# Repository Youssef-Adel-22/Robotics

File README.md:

# Robotics
Line Follower Robot Hardware and software design

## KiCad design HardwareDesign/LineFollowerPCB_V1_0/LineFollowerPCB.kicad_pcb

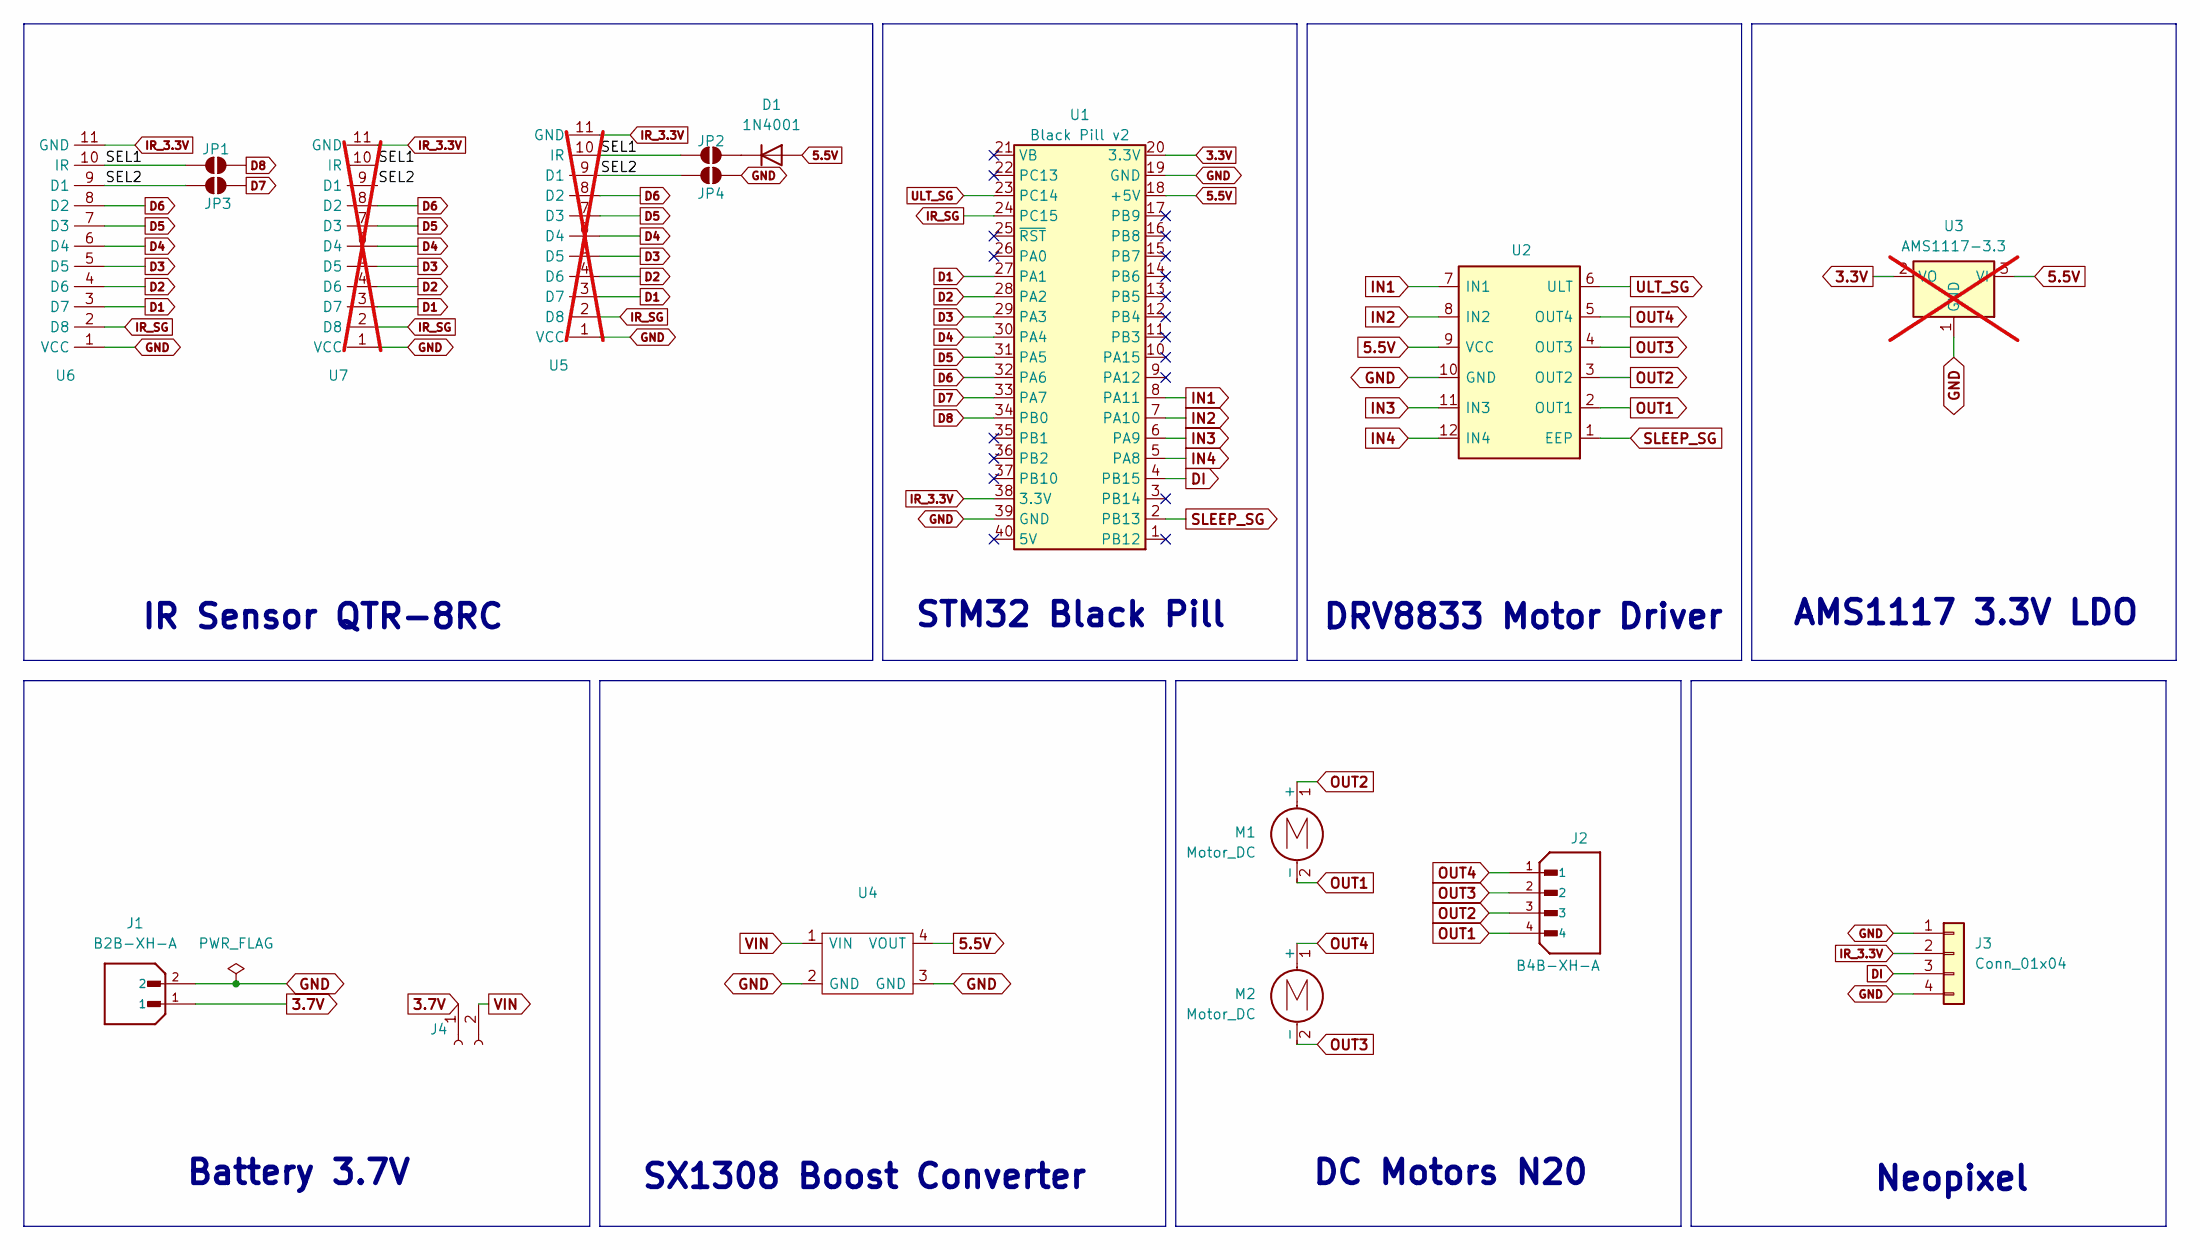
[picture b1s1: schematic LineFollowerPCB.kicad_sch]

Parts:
D1: 1N4001; D_DO-41_SOD81_P10.16mm_Horizontal
J1: B2B-XH-A; JST_B2B-XH-A; PARTREV N/A
J2: B4B-XH-A; JST_B4B-XH-A; PARTREV 7/4/21
J3: Conn_01x04; PinHeader_1x04_P2.54mm_Horizontal
J4: Conn_01x02_Socket; PinHeader_1x02_P2.54mm_Vertical
JP1, JP2, JP3, JP4: SolderJumper_3_Open; SolderJumper-2_P1.3mm_Open_RoundedPad1.0x1.5mm
M1, M2: Motor_DC; N20DCMotor
U1: Black Pill v2; Module_BlackPill_v2
U2: DRV8833
U3: AMS1117-3.3; PinHeader_1x03_P2.54mm_Vertical; not fitted
U4: SX1308
U5, U7: PinHeader_1x11_P2.54mm_Vertical; not fitted
U6: PinHeader_1x11_P2.54mm_Vertical

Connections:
3.3V: U1.20 (3.3V), U3.2 (VO)
3.7V: J1.1, J4.1
5.5V: D1.2 (A), U1.18 (+5V), U2.9 (VCC), U3.3 (VI), U4.4 (VOUT)
/SEL1: JP1.1 (A), JP2.2 (B), U5.10 (D8), U6.10 (D8), U7.10 (IR)
/SEL2: JP3.2 (B), JP4.1 (A), U5.9 (D7), U6.9 (D7), U7.9 (D1)
D1: U1.27 (PA1), U5.3 (D1), U6.3 (D1), U7.3 (D7)
D2: U1.28 (PA2), U5.4 (D2), U6.4 (D2), U7.4 (D6)
D3: U1.29 (PA3), U5.5 (D3), U6.5 (D3), U7.5 (D5)
D4: U1.30 (PA4), U5.6 (D4), U6.6 (D4), U7.6 (D4)
D5: U1.31 (PA5), U5.7 (D5), U6.7 (D5), U7.7 (D3)
D6: U1.32 (PA6), U5.8 (D6), U6.8 (D6), U7.8 (D2)
D7: JP3.1 (A), U1.33 (PA7)
D8: JP1.2 (B), U1.34 (PB0)
DI: J3.3, U1.4 (PB15)
GND: J1.2, J3.1, J3.4, JP4.2 (B), U1.19 (GND), U1.39 (GND), U2.10 (GND), U3.1 (GND), U4.2 (GND), U4.3 (GND), U5.1 (GND), U6.1 (GND), U7.1 (VCC)
IN1: U1.8 (PA11), U2.7 (IN1)
IN2: U1.7 (PA10), U2.8 (IN2)
IN3: U1.6 (PA9), U2.11 (IN3)
IN4: U1.5 (PA8), U2.12 (IN4)
IR_3.3V: J3.2, U1.38 (3.3V), U5.11 (VCC), U6.11 (VCC), U7.11 (GND)
IR_SG: U1.24 (PC15), U5.2 (IR), U6.2 (IR), U7.2 (D8)
unnamed: D1.1 (K), JP2.1 (A)
OUT1: J2.4, M1.2 (-), U2.2 (OUT1)
OUT2: J2.3, M1.1 (+), U2.3 (OUT2)
OUT3: J2.2, M2.2 (-), U2.4 (OUT3)
OUT4: J2.1, M2.1 (+), U2.5 (OUT4)
SLEEP_SG: U1.2 (PB13), U2.1 (EEP)
ULT_SG: U1.23 (PC14), U2.6 (ULT)
VIN: J4.2, U4.1 (VIN)

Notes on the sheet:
AMS1117 3.3V LDO
Neopixel
IR Sensor QTR-8RC
Battery 3.7V
STM32 Black Pill
SX1308 Boost Converter
DRV8833 Motor Driver
DC Motors N20

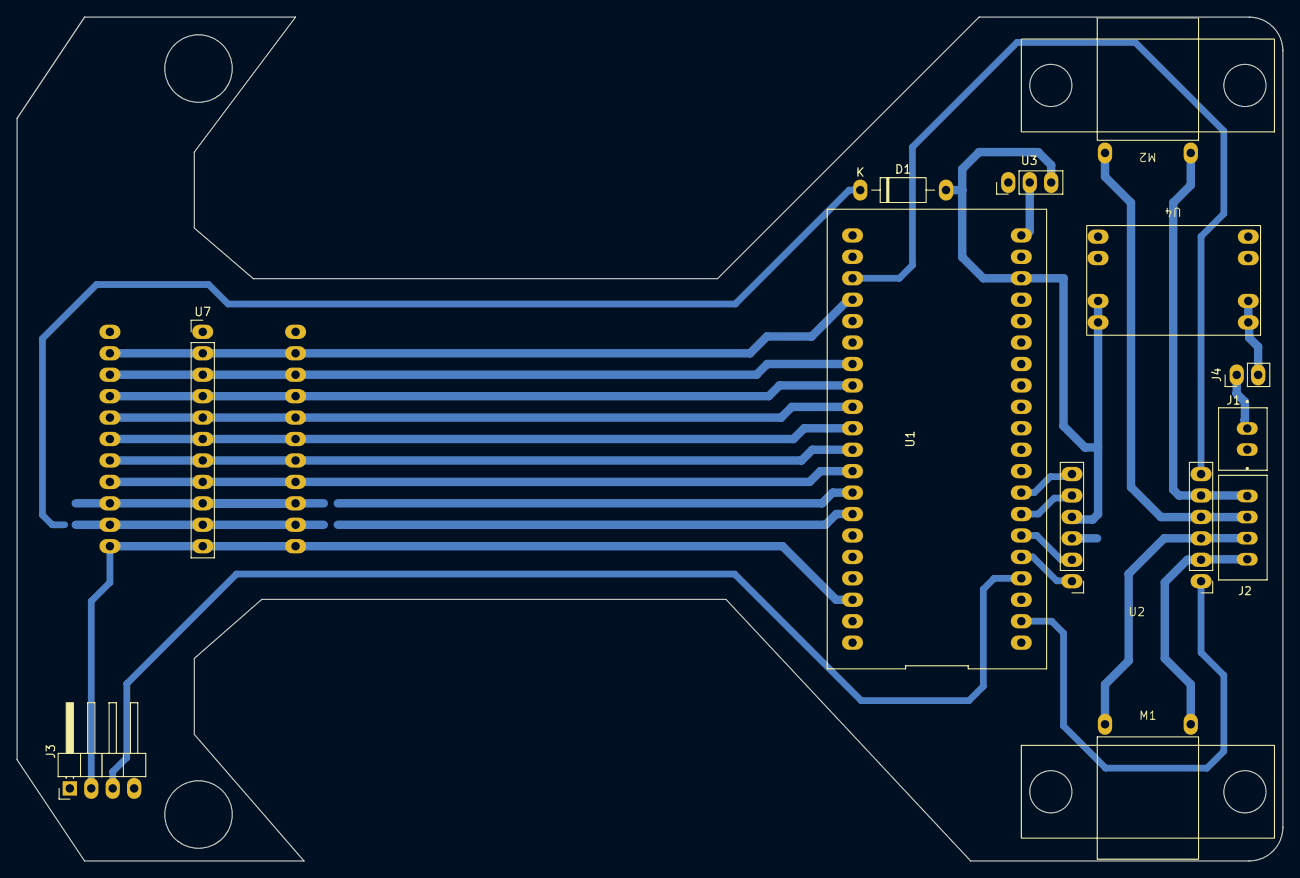
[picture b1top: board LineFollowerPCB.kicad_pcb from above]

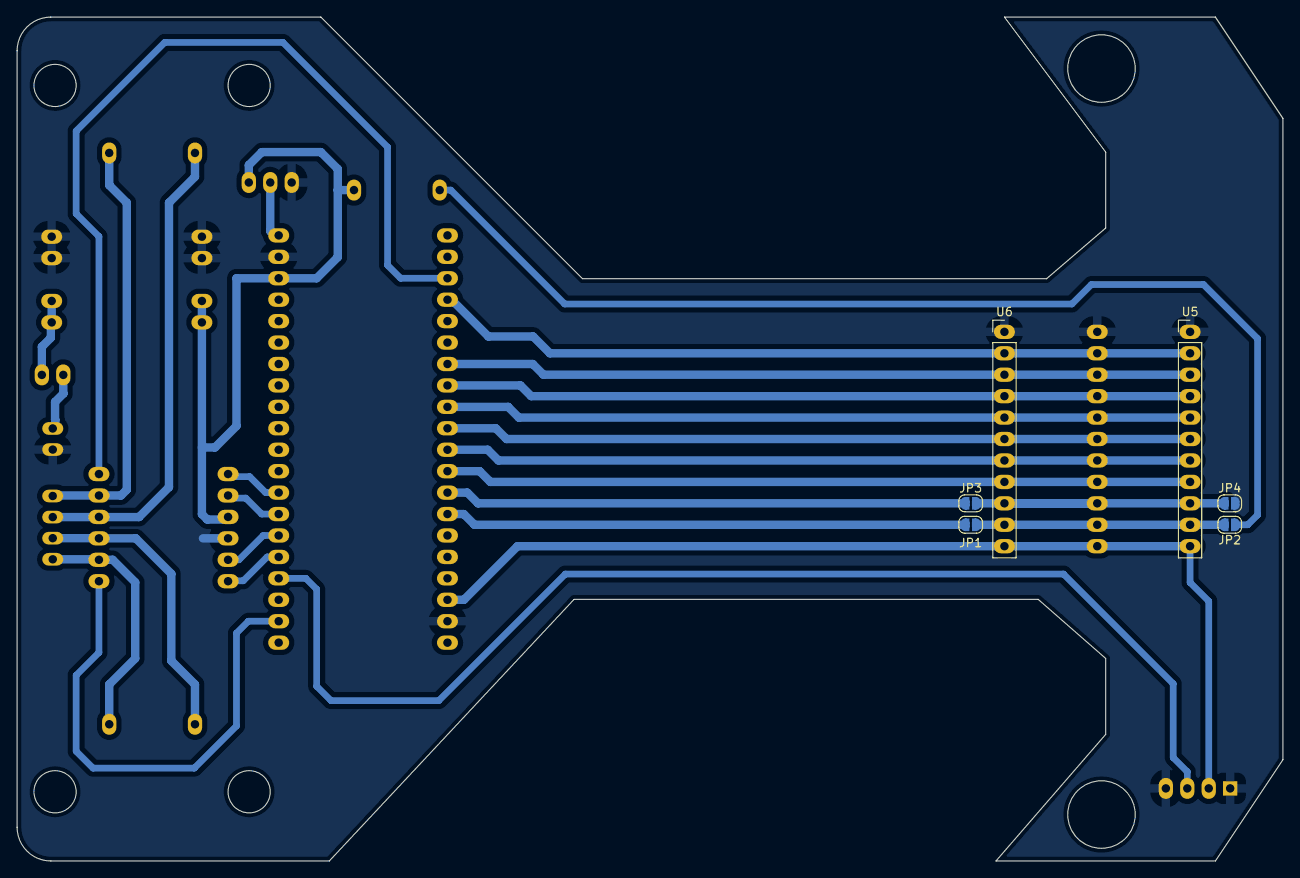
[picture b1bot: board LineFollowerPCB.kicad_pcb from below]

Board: 2 copper layers, 150.0 x 100.0 mm, 18 parts (6 on the bottom side), 29 nets.

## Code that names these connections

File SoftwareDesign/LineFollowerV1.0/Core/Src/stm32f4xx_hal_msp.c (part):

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    __HAL_RCC_GPIOA_CLK_ENABLE();
    __HAL_RCC_GPIOB_CLK_ENABLE();
    /**ADC1 GPIO Configuration
    PA1     ------> ADC1_IN1
    PA2     ------> ADC1_IN2
    PA3     ------> ADC1_IN3
    PA4     ------> ADC1_IN4
    PA5     ------> ADC1_IN5
    PA6     ------> ADC1_IN6
    PA7     ------> ADC1_IN7
    PB0     ------> ADC1_IN8
    */
    GPIO_InitStruct.Pin = GPIO_PIN_1|GPIO_PIN_2|GPIO_PIN_3|GPIO_PIN_4
                          |GPIO_PIN_5|GPIO_PIN_6|GPIO_PIN_7;
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    __HAL_RCC_ADC1_CLK_DISABLE();

    /**ADC1 GPIO Configuration
    PA1     ------> ADC1_IN1
    PA2     ------> ADC1_IN2
    PA3     ------> ADC1_IN3
    PA4     ------> ADC1_IN4
    PA5     ------> ADC1_IN5
    PA6     ------> ADC1_IN6
    PA7     ------> ADC1_IN7
    PB0     ------> ADC1_IN8
    */
    HAL_GPIO_DeInit(GPIOA, GPIO_PIN_1|GPIO_PIN_2|GPIO_PIN_3|GPIO_PIN_4
                          |GPIO_PIN_5|GPIO_PIN_6|GPIO_PIN_7);
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    __HAL_RCC_GPIOB_CLK_ENABLE();
    /**SPI2 GPIO Configuration
    PB10     ------> SPI2_SCK
    PB15     ------> SPI2_MOSI
    */
    GPIO_InitStruct.Pin = GPIO_PIN_10|GPIO_PIN_15;
    GPIO_InitStruct.Mode = GPIO_MODE_AF_PP;
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
    /**SPI2 GPIO Configuration
    PB10     ------> SPI2_SCK
    PB15     ------> SPI2_MOSI
    */
    HAL_GPIO_DeInit(GPIOB, GPIO_PIN_10|GPIO_PIN_15);

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
    __HAL_RCC_GPIOA_CLK_ENABLE();
    /**TIM1 GPIO Configuration
    PA8     ------> TIM1_CH1
    PA9     ------> TIM1_CH2
    PA10     ------> TIM1_CH3
    PA11     ------> TIM1_CH4
    */
    GPIO_InitStruct.Pin = IN4_Pin|IN3_Pin|IN2_Pin|IN1_Pin;
    GPIO_InitStruct.Mode = GPIO_MODE_AF_PP;
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
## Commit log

2025-08-17 Initial PCB design of Line follower robot
2025-08-24 The LineFollower PCB design Version 2.0 with Cytron sensor
2025-08-25 - Update the schematic design - Fix the pins arrangment of the cytron sensor - Create the Cytron sensor footprint - Add the Cytron sensor 3D model - Add the 1N4001 doide - Update the layout
2025-08-31 - Add Shunt bridge for power switching ON-OFF - Edit DC motor footprint library - Add solder jumber for select between QTR / Cytron sensors
2025-09-03 Add initial software design included calibration function
2025-09-03 Add 1N4001 doide and connect the 5V power signal to the sensor
2025-09-06 Successfully save the calibration data in the flash memory and retrieve it at startup
2025-09-08 Hardware changes: - Change the Neopixel pin to B15 instead of B12 - Add IR pinheader strip - Generate production files
2025-09-13 Software changes: - Implement Neopixel write function using SPI - Implement initial Line follower state machine
2025-09-19 Software update - Implement initial line follower test code
2025-09-25 Hardware and software update: - Upuated STM32 and DC motors footprints - Updated the Gerber files - Implement P from the PID algorithm
2025-09-27 Software changes - Increased SETSPEED from 950 to 1000 - Fix LEFT and Right Functions in State machine - Move Forwared function to defualt case in state machine
2025-09-27 Software updates: - Implement the KD of the PID algorithm - Increased the SETSPEED to 1100 and get 30Sec score
2025-09-28 Software updates: - Retune PID (KP=30, KD=40, MIN_SPEED=700, and ROTATION_SPEED=800) - Make Left, Right, and Forward functions stateic inline
2025-09-28 Software updates: - Retune to fix rotation issue in right DC Motor
2025-09-29 Software updatees: - Updated the state machine - Rename the Idle state to Ready state - Fix pin mapping of the Motor driver - Add comments on Main.c
2025-11-08 Software Updates - Fix the PID error distribution values to be 2 to 16 instead of 0 to 14 - Add lost code - Increase rotate cases

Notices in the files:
SoftwareDesign/LineFollowerV1.0/Core/Src/stm32f4xx_hal_msp.c:
Copyright (c) 2025 STMicroelectronics.
All rights reserved.
This software is licensed under terms that can be found in the LICENSE file
